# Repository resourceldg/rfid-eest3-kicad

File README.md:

# Control de acceso RFID EEST3

Diseño electrónico en KiCad 10 para un sistema de acceso escolar basado en ESP32, RC522, sensores y control de cerradura de 12 V.

## Estado actual del proyecto

Hay una placa de prueba de 140 × 100 mm, doble cara, **ruteada y con el DRC
limpio**: 348 pistas, 8 vías, dos planos de masa separados que se tocan en un
solo punto, y ninguna infracción de margen, cobre, alivio térmico ni
serigrafía. Los tres "no conectados" que informa el DRC son deliberados.

**No está lista para fabricar.** Faltan las mediciones de banco, la
verificación mecánica de los conectores y, sobre todo, medir el módulo ESP32-S3
para borrar la hilera de pines que sobra en J13. Los tres bloqueos están
detallados en [PENDIENTES.md](rfid-control-acceso-eest3/PENDIENTES.md).

## Ver todo el circuito de un vistazo

Las seis hojas del esquema son el documento valido, pero estan separadas y la
hoja raiz no dibuja como se relacionan. Para eso esta
[RESUMEN_ELECTRICO.kicad_sch](rfid-control-acceso-eest3/RESUMEN_ELECTRICO.kicad_sch):
una sola hoja A2 con los 67 componentes, sus simbolos y valores, el cableado de
cada bloque y el ESP32 en el centro. Es documentacion y **no forma parte de la
jerarquia del proyecto**: se abre sola.

```sh
python3 tools/esquema_resumen.py     # regenera la hoja desde el netlist real
kicad-cli sch export pdf -o rfid-control-acceso-eest3/RESUMEN_ELECTRICO.pdf \
    rfid-control-acceso-eest3/RESUMEN_ELECTRICO.kicad_sch
```

El generador se verifica solo: exporta el netlist de la hoja que acaba de
escribir y lo compara nodo por nodo contra el de las seis hojas. Si no coincide,
falla.

## Documentos de referencia

- Qué falta para fabricar: [rfid-control-acceso-eest3/PENDIENTES.md](rfid-control-acceso-eest3/PENDIENTES.md)
- Revisión técnica y riesgos: [rfid-control-acceso-eest3/INFORME_ESQUEMA.md](rfid-control-acceso-eest3/INFORME_ESQUEMA.md)
- Mediciones que faltan: [rfid-control-acceso-eest3/CHECKLIST_PREPCB.md](rfid-control-acceso-eest3/CHECKLIST_PREPCB.md)
- Por qué el cobre está donde está: [rfid-control-acceso-eest3/GUIA_RUTEO.md](rfid-control-acceso-eest3/GUIA_RUTEO.md)

## Próximo paso recomendado

Medir la separación real entre hileras del ESP32-S3 DevKit y borrar la hilera
sobrante de J13. Es el único bloqueo que no necesita instrumental: alcanza con
un calibre y el módulo en la mano.

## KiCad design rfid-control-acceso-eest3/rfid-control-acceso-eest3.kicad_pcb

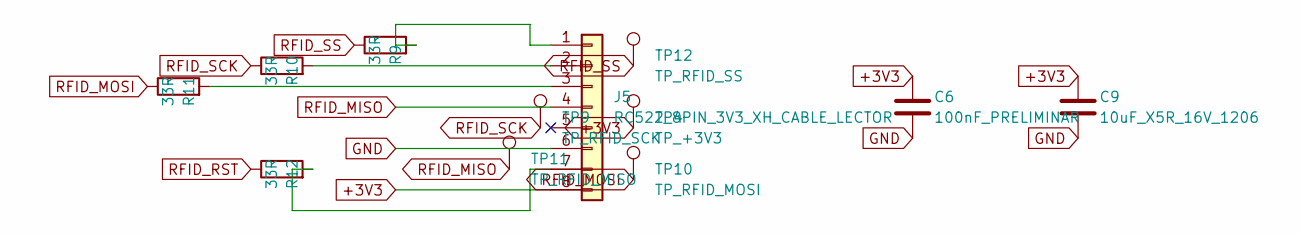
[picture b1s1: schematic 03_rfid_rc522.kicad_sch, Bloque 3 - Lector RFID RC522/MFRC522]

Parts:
C6: 100nF_PRELIMINAR; C_Disc_D5.0mm_W2.5mm_P5.00mm
C9: 10uF_X5R_16V_1206; C_1206_3216Metric
J5: RC522_8PIN_3V3_XH_CABLE_LECTOR; JST_XH_S8B-XH-A_1x08_P2.50mm_Horizontal
R9, R10, R11, R12: 33R; R_Axial_DIN0207_L6.3mm_D2.5mm_P10.16mm_Horizontal
TP4: TP_+3V3; TestPoint_THTPad_D2.0mm_Drill1.0mm
TP9: TP_RFID_SCK; TestPoint_THTPad_D2.0mm_Drill1.0mm
TP10: TP_RFID_MOSI; TestPoint_THTPad_D2.0mm_Drill1.0mm
TP11: TP_RFID_MISO; TestPoint_THTPad_D2.0mm_Drill1.0mm
TP12: TP_RFID_SS; TestPoint_THTPad_D2.0mm_Drill1.0mm

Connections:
+3V3: C6.1, C9.1, J5.8, TP4.1 (1_1); also elsewhere on the board
GND: C6.2, C9.2, J5.6; also elsewhere on the board
unnamed: J5.1, R9.2
unnamed: J5.2, R10.2
unnamed: J5.3, R11.2
unnamed: J5.7, R12.2
RFID_MISO: J5.4, TP11.1 (1_1); also elsewhere on the board
RFID_MOSI: R11.1, TP10.1 (1_1); also elsewhere on the board
RFID_RST: R12.1; also elsewhere on the board
RFID_SCK: R10.1, TP9.1 (1_1); also elsewhere on the board
RFID_SS: R9.1, TP12.1 (1_1); also elsewhere on the board

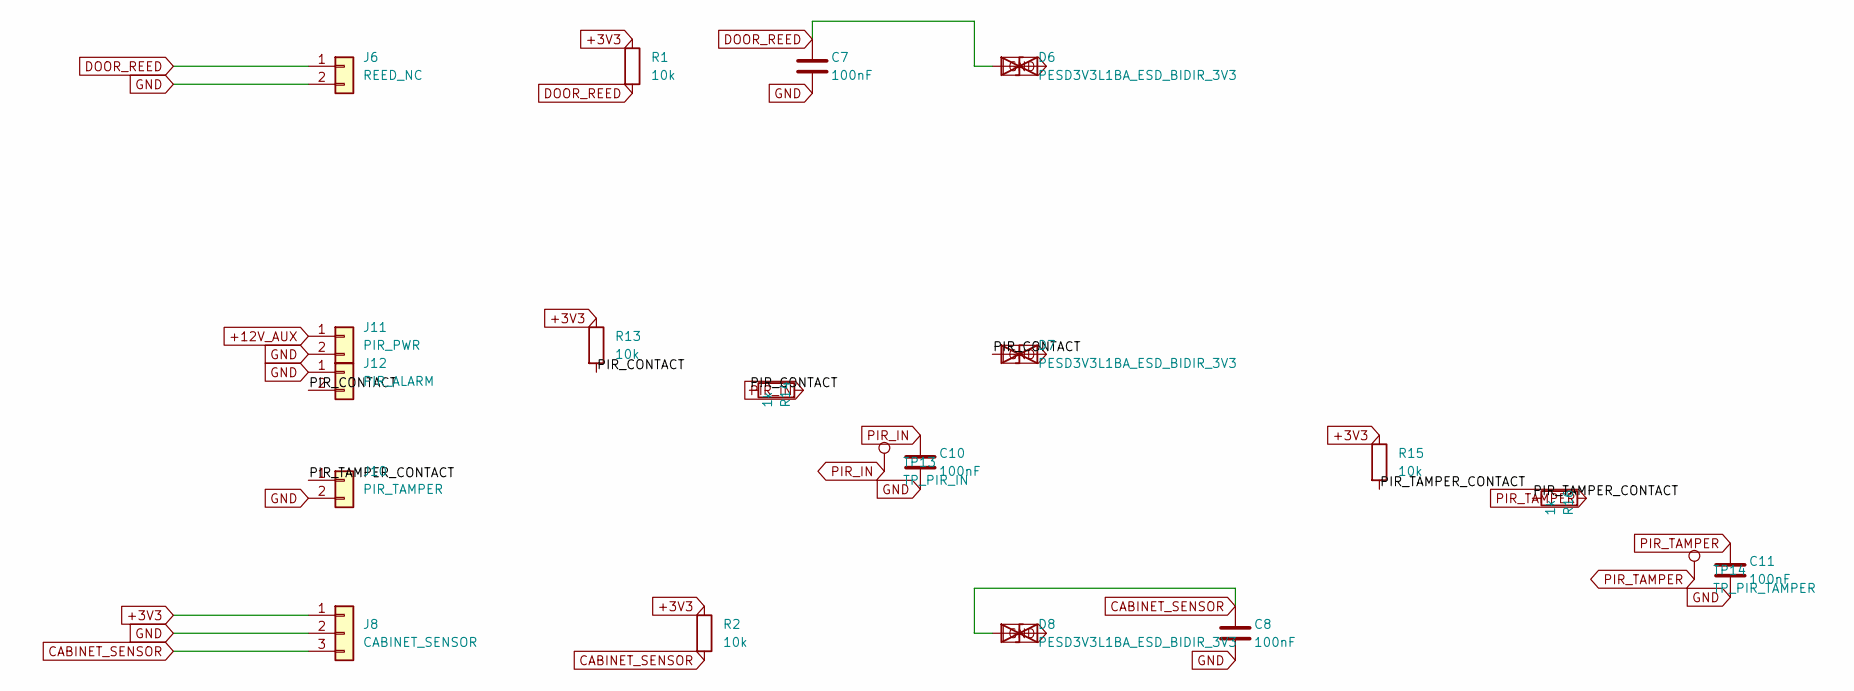
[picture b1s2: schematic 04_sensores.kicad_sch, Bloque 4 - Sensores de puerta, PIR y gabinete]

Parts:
C7, C8, C10, C11: 100nF; C_Disc_D5.0mm_W2.5mm_P5.00mm
D6, D7, D8: PESD3V3L1BA_ESD_BIDIR_3V3; D_SOD-323; MPN PESD3V3L1BA,115
J6: REED_NC; TerminalBlock_RND_205-00232_1x02_P5.08mm_Horizontal
J8: CABINET_SENSOR; TerminalBlock_RND_205-00233_1x03_P5.08mm_Horizontal
J10: PIR_TAMPER; TerminalBlock_RND_205-00232_1x02_P5.08mm_Horizontal
J11: PIR_PWR; TerminalBlock_RND_205-00232_1x02_P5.08mm_Horizontal
J12: PIR_ALARM; TerminalBlock_RND_205-00232_1x02_P5.08mm_Horizontal
R1, R2, R13, R15: 10k; R_Axial_DIN0207_L6.3mm_D2.5mm_P10.16mm_Horizontal
R14, R16: 1k; R_Axial_DIN0207_L6.3mm_D2.5mm_P10.16mm_Horizontal
TP13: TP_PIR_IN; TestPoint_THTPad_D2.0mm_Drill1.0mm
TP14: TP_PIR_TAMPER; TestPoint_THTPad_D2.0mm_Drill1.0mm

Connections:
+3V3: J8.1, R1.1, R2.1, R13.1, R15.1; also elsewhere on the board
+12V_AUX: J11.1; also elsewhere on the board
/4_SENSORES/PIR_CONTACT: D7.1 (A1), J12.2, R13.2, R14.1
/4_SENSORES/PIR_TAMPER_CONTACT: J10.1, R15.2, R16.1
CABINET_SENSOR: C8.1, D8.1 (A1), J8.3, R2.2; also elsewhere on the board
DOOR_REED: C7.1, D6.1 (A1), J6.1, R1.2; also elsewhere on the board
GND: C7.2, C8.2, C10.2, C11.2, D6.2 (A2), D7.2 (A2), D8.2 (A2), J6.2, J8.2, J10.2, J11.2, J12.1; also elsewhere on the board
PIR_IN: C10.1, R14.2, TP13.1 (1_1); also elsewhere on the board
PIR_TAMPER: C11.1, R16.2, TP14.1 (1_1); also elsewhere on the board

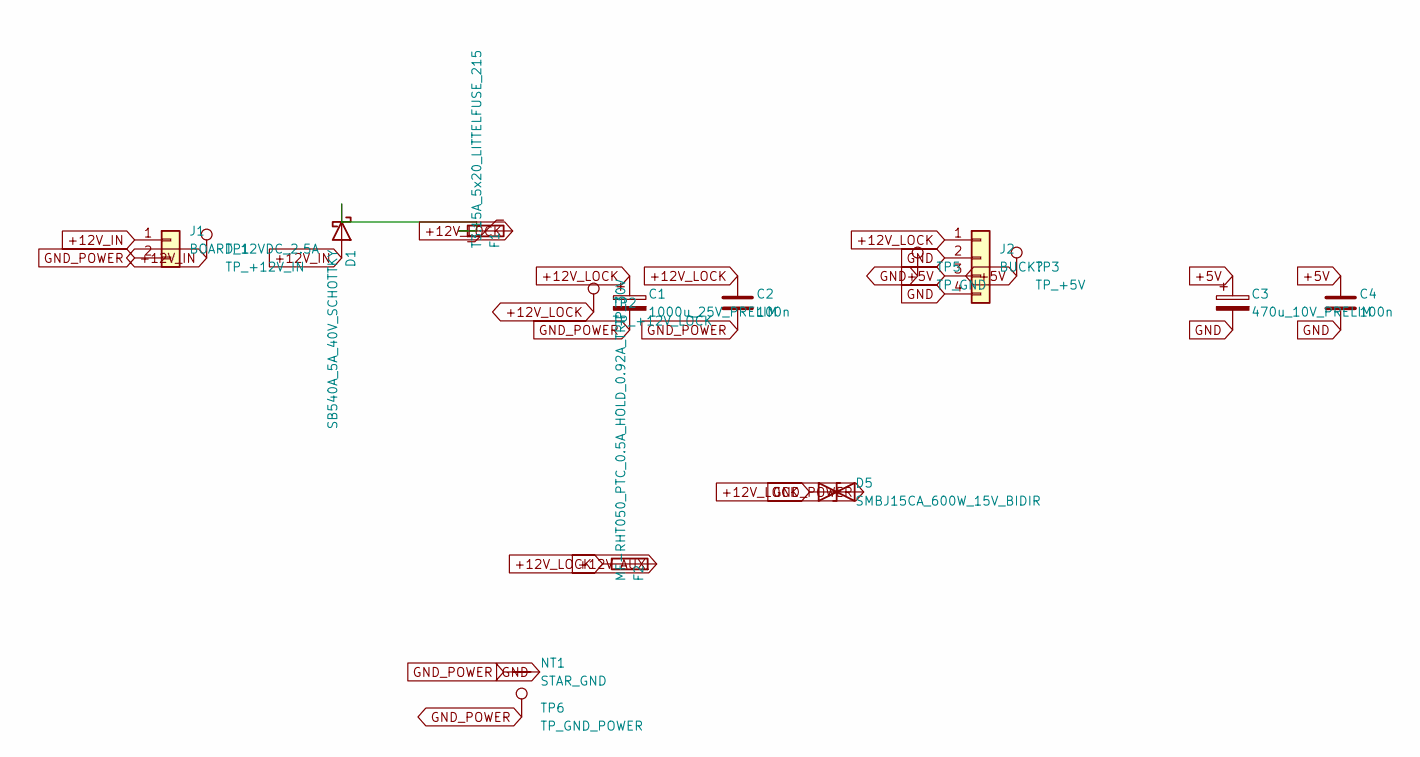
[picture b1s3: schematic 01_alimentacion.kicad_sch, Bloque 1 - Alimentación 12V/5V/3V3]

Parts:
C1: 1000u_25V_PRELIM; CP_Radial_D16.0mm_P7.50mm
C2, C4: 100n; C_Disc_D5.0mm_W2.5mm_P5.00mm
C3: 470u_10V_PRELIM; CP_Radial_D10.0mm_P5.00mm_P7.50mm
D1: SB540A_5A_40V_SCHOTTKY; D_DO-201AD_P15.24mm_Horizontal; MPN SB540A-E3/54
D5: SMBJ15CA_600W_15V_BIDIR; D_SMB; MPN SMBJ15CA
F1: T3.15A_5x20_LITTELFUSE_215; Fuseholder_Clip-5x20mm_Bel_FC-203-22_Lateral_P17.80x5.00mm_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; MPN 021503.15MXP + FC-203-22
F2: MF-RHT050_PTC_0.5A_HOLD_0.92A_TRIP_30V; Fuse_Bourns_MF-RHT050; MPN MF-RHT050
J1: BOARD_12VDC_2.5A; TerminalBlock_RND_205-00232_1x02_P5.08mm_Horizontal
J2: BUCK?; TerminalBlock_RND_205-00234_1x04_P5.08mm_Horizontal
NT1: STAR_GND; NetTie-2_THT_Pad1.0mm
TP1: TP_+12V_IN; TestPoint_THTPad_D2.0mm_Drill1.0mm
TP2: TP_+12V_LOCK; TestPoint_THTPad_D2.0mm_Drill1.0mm
TP3: TP_+5V; TestPoint_THTPad_D2.0mm_Drill1.0mm
TP5: TP_GND; TestPoint_THTPad_D2.0mm_Drill1.0mm
TP6: TP_GND_POWER; TestPoint_THTPad_D2.0mm_Drill1.0mm

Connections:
+5V: C3.1, C4.1, J2.3, TP3.1 (1_1); also elsewhere on the board
+12V_AUX: F2.2; also elsewhere on the board
+12V_IN: D1.2 (A), J1.1, TP1.1 (1_1)
+12V_LOCK: C1.1, C2.1, D5.1 (A1), F1.2, F2.1, J2.1, TP2.1 (1_1); also elsewhere on the board
GND: C3.2, C4.2, J2.2, J2.4, NT1.2, TP5.1 (1_1); also elsewhere on the board
GND_POWER: C1.2, C2.2, D5.2 (A2), J1.2, NT1.1, TP6.1 (1_1); also elsewhere on the board
unnamed: D1.1 (K), F1.1

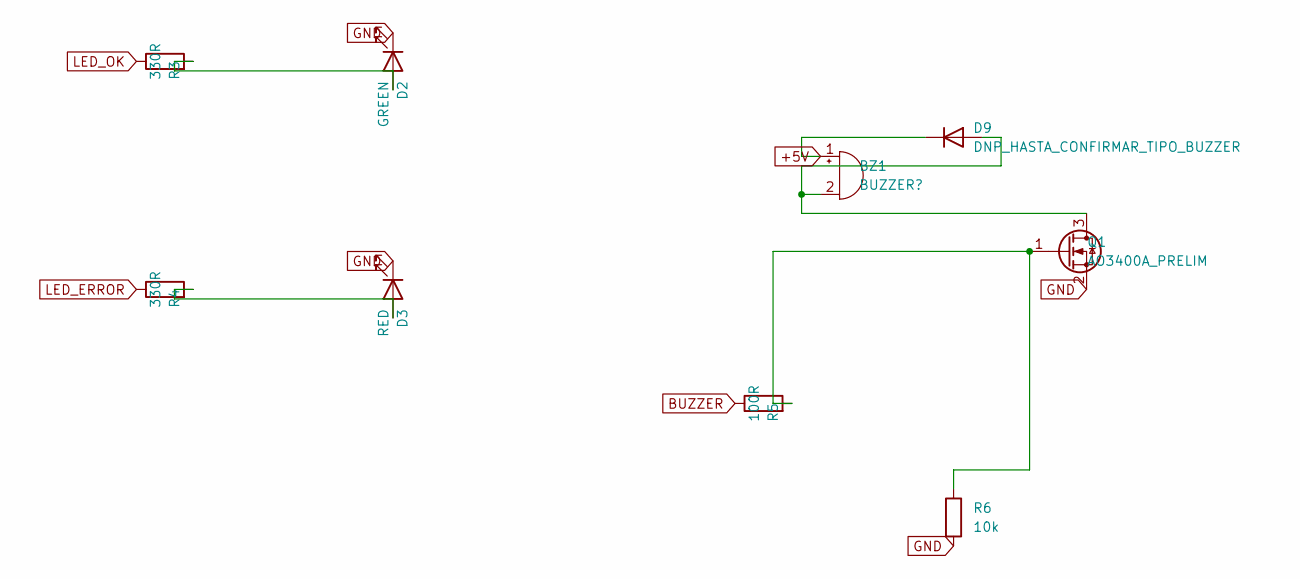
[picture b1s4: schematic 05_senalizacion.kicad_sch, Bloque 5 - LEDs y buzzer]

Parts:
BZ1: BUZZER?; Buzzer_12x9.5RM7.6
D2: GREEN; LED_D5.0mm
D3: RED; LED_D5.0mm
D9: DNP_HASTA_CONFIRMAR_TIPO_BUZZER; D_DO-35_SOD27_P10.16mm_Horizontal
Q1: AO3400A_PRELIM; SOT-23
R3, R4: 330R; R_Axial_DIN0207_L6.3mm_D2.5mm_P10.16mm_Horizontal
R5: 100R; R_Axial_DIN0207_L6.3mm_D2.5mm_P10.16mm_Horizontal
R6: 10k; R_Axial_DIN0207_L6.3mm_D2.5mm_P10.16mm_Horizontal

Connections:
+5V: BZ1.1 (+), D9.1 (K); also elsewhere on the board
BUZZER: R5.1; also elsewhere on the board
GND: D2.1 (K), D3.1 (K), Q1.2 (S), R6.2; also elsewhere on the board
LED_ERROR: R4.1; also elsewhere on the board
LED_OK: R3.1; also elsewhere on the board
unnamed: BZ1.2 (-), D9.2 (A), Q1.3 (D)
unnamed: D2.2 (A), R3.2
unnamed: D3.2 (A), R4.2
unnamed: Q1.1 (G), R5.2, R6.1

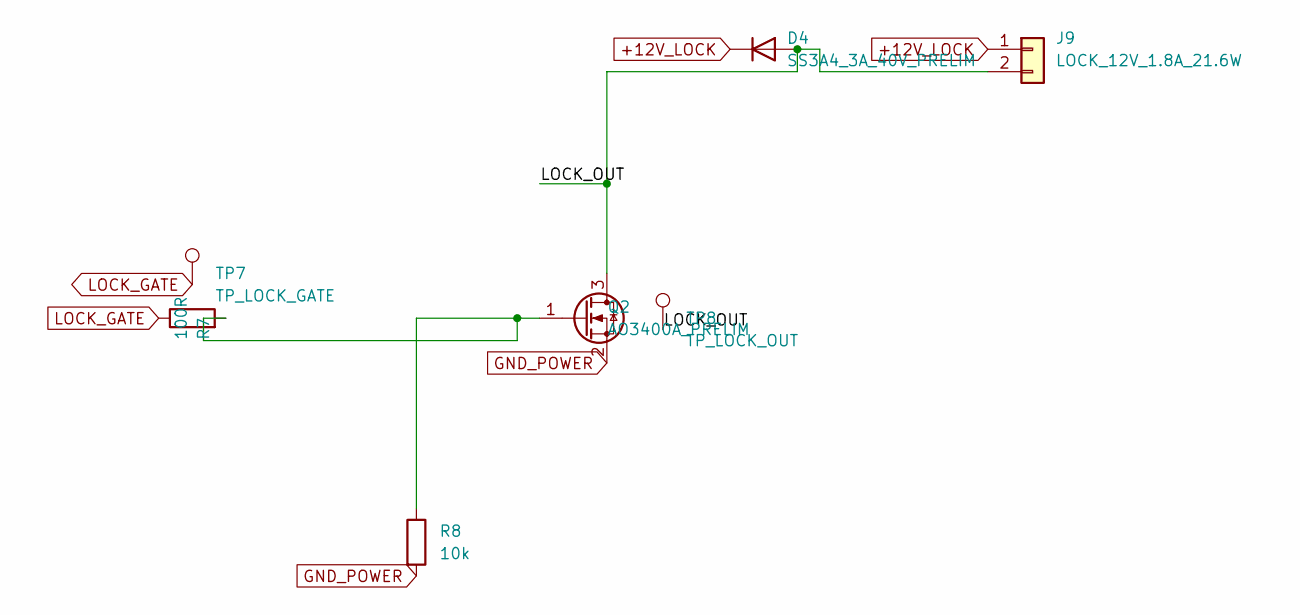
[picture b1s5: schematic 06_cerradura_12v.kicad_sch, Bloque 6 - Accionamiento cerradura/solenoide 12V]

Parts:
D4: SS3A4_3A_40V_PRELIM; D_SMA
J9: LOCK_12V_1.8A_21.6W; TerminalBlock_RND_205-00232_1x02_P5.08mm_Horizontal
Q2: AO3400A_PRELIM; SOT-23
R7: 100R; R_Axial_DIN0207_L6.3mm_D2.5mm_P10.16mm_Horizontal
R8: 10k; R_Axial_DIN0207_L6.3mm_D2.5mm_P10.16mm_Horizontal
TP7: TP_LOCK_GATE; TestPoint_THTPad_D2.0mm_Drill1.0mm
TP8: TP_LOCK_OUT; TestPoint_THTPad_D2.0mm_Drill1.0mm

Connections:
+12V_LOCK: D4.1 (K), J9.1; also elsewhere on the board
/6_CERRADURA_12V/LOCK_OUT: D4.2 (A), J9.2, Q2.3 (D), TP8.1 (1_1)
GND_POWER: Q2.2 (S), R8.2; also elsewhere on the board
LOCK_GATE: R7.1, TP7.1 (1_1); also elsewhere on the board
unnamed: Q2.1 (G), R7.2, R8.1

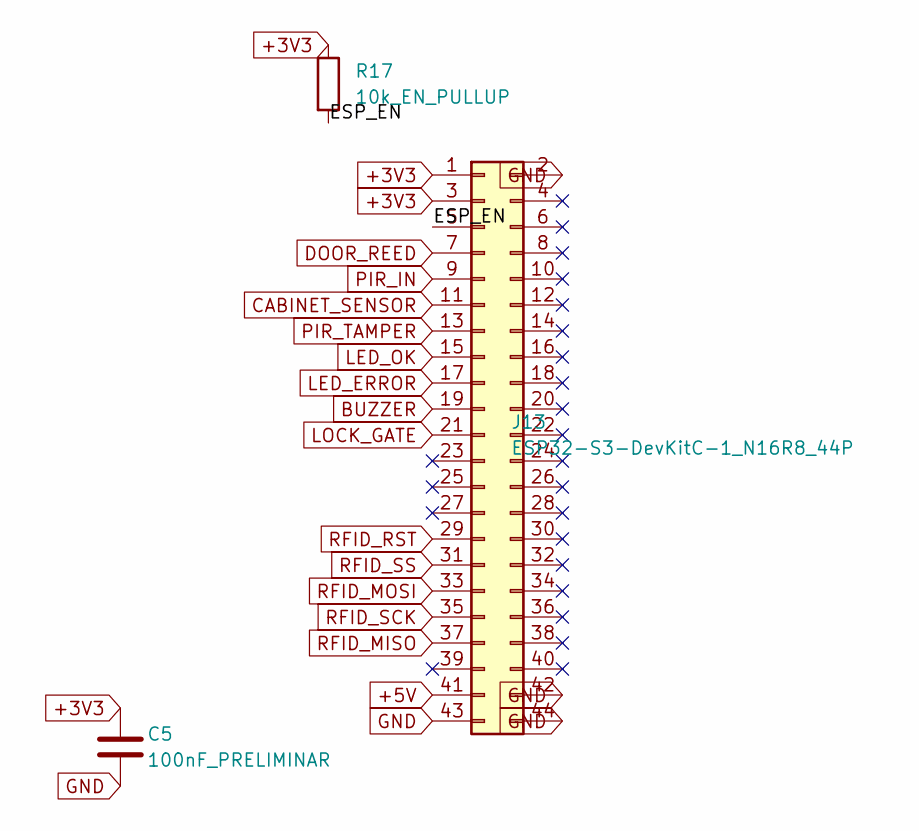
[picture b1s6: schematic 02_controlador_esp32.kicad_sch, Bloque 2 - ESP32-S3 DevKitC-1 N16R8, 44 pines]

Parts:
C5: 100nF_PRELIMINAR; C_Disc_D5.0mm_W2.5mm_P5.00mm
J13: ESP32-S3-DevKitC-1_N16R8_44P; ESP32-S3-44P_SOCKET_DUAL_22.86_25.40
R17: 10k_EN_PULLUP; R_Axial_DIN0207_L6.3mm_D2.5mm_P10.16mm_Horizontal

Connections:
+3V3: C5.1, J13.1, J13.3, R17.1; also elsewhere on the board
+5V: J13.41; also elsewhere on the board
/2_CONTROLADOR_ESP32/ESP_EN: J13.5, R17.2
BUZZER: J13.19; also elsewhere on the board
CABINET_SENSOR: J13.11; also elsewhere on the board
DOOR_REED: J13.7; also elsewhere on the board
GND: C5.2, J13.2, J13.42, J13.43, J13.44; also elsewhere on the board
LED_ERROR: J13.17; also elsewhere on the board
LED_OK: J13.15; also elsewhere on the board
LOCK_GATE: J13.21; also elsewhere on the board
PIR_IN: J13.9; also elsewhere on the board
PIR_TAMPER: J13.13; also elsewhere on the board
RFID_MISO: J13.37; also elsewhere on the board
RFID_MOSI: J13.33; also elsewhere on the board
RFID_RST: J13.29; also elsewhere on the board
RFID_SCK: J13.35; also elsewhere on the board
RFID_SS: J13.31; also elsewhere on the board

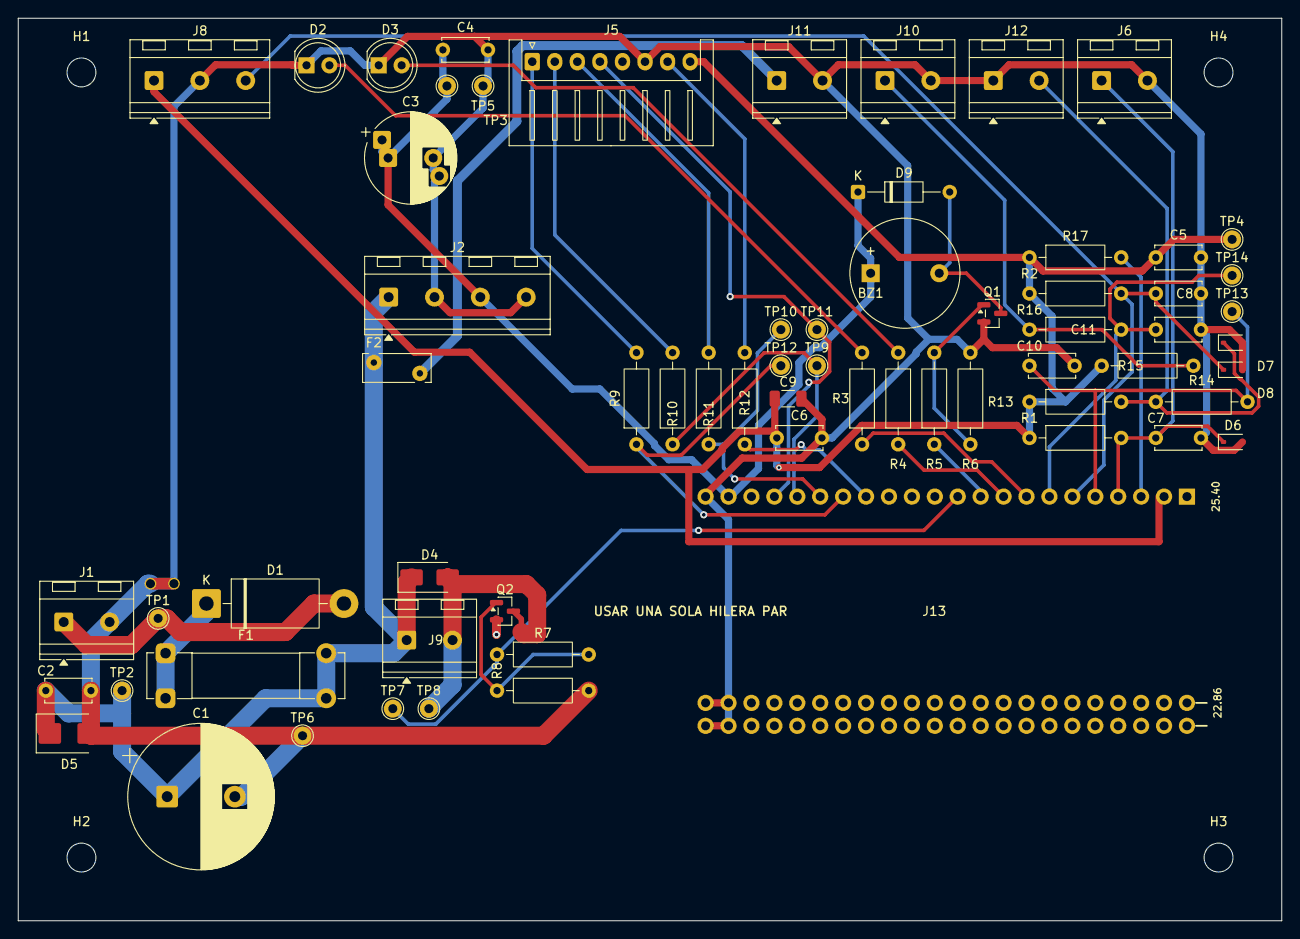
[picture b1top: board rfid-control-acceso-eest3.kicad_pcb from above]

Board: 2 copper layers, 140.0 x 100.0 mm, 71 parts (0 on the bottom side), 34 nets.

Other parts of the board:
H1, H2, H3, H4: MOUNTING_HOLE_3.2_PROVISIONAL; MountingHole_3.2mm_M3
